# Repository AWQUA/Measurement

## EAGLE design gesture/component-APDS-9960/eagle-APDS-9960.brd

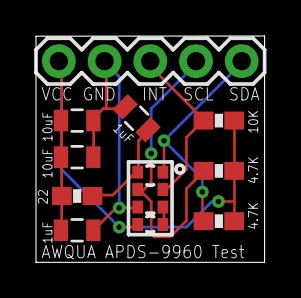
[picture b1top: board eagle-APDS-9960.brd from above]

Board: 2 copper layers, 12.7 x 12.6 mm, 10 parts (0 on the bottom side), 7 nets.

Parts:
C1, C4: 10uF; 0805
C2, C3: 1uF; 0805
JP1: 1X05
R1: 10K; 0603-RES
R2, R3: 4.7K; 0603-RES
R4: 22; 0603-RES
U1: APDS-9960

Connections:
GND: C1.1, C2.2, C3.1, C4.1, JP1.4, U1.6
INT: JP1.3, R1.1, U1.2
unnamed: U1.3, U1.4
unnamed: C3.2, R4.1, U1.8
SCL: JP1.2, R2.1, U1.7
SDA: JP1.1, R3.1, U1.1
VCC: C1.2, C2.1, C4.2, JP1.5, R1.2, R2.2, R3.2, R4.2, U1.5

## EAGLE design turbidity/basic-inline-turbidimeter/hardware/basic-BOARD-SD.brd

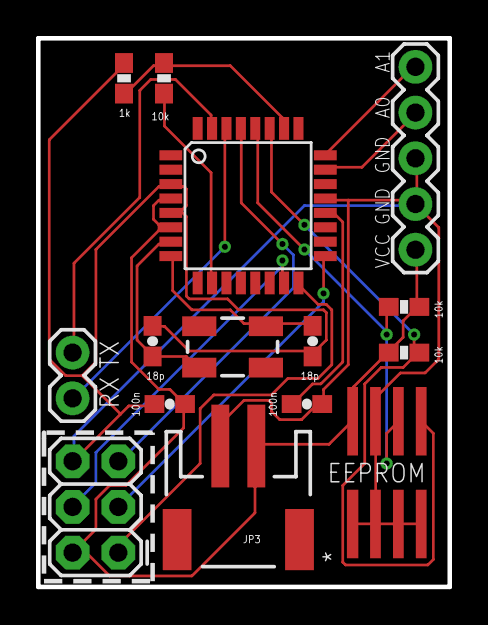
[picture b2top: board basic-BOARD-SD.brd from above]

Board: 2 copper layers, 22.9 x 30.5 mm, 17 parts (1 on the bottom side), 17 nets.

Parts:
C1, C2: 18p; 0603-CAP
C5, C8: 100n; 0603-CAP
EEPROM: AT24C256; SOIC8-LONGPAD
FRAME1: FRAME-LETTER; CREATIVE_COMMONS
IC1: MEGA8-AI; TQFP32-08
JP1: M02PTH; 1X02
JP2: 2X3
JP3: M02-JST-2MM-SMT; JST-2-SMD
JP4: 1X05
R1, R4, R5: 10k; 0603-RES
R2: 1k; 0603-RES
U$1: OSHW-LOGO-S
Y1: CRYSTAL-SMD-5X3

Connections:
AREF: C5.2, IC1.20
GND: C1.1, C2.1, C5.1, C8.2, EEPROM.1, EEPROM.2, EEPROM.3, EEPROM.4, EEPROM.7, IC1.3, IC1.5, IC1.21, JP2.6, JP3.2, JP4.3, JP4.4, R2.1
MISO: IC1.16, JP2.1
MOSI: IC1.15, JP2.4
PC0: IC1.23, JP4.2
PC1: IC1.24, JP4.1
PC3: IC1.26, R1.2, R2.2
PD6: IC1.10, R1.1
Q1: C2.2, IC1.8, Y1.1
Q2: C1.2, IC1.7, Y1.3
RST: IC1.29, JP2.5
RX: IC1.30, JP1.1
SCK: IC1.17, JP2.3
SCL: EEPROM.6, IC1.28, R5.2
SDA: EEPROM.5, IC1.27, R4.2
TX: IC1.31, JP1.2
VCC: C8.1, EEPROM.8, IC1.4, IC1.6, JP2.2, JP3.1, JP4.5, R4.1, R5.1

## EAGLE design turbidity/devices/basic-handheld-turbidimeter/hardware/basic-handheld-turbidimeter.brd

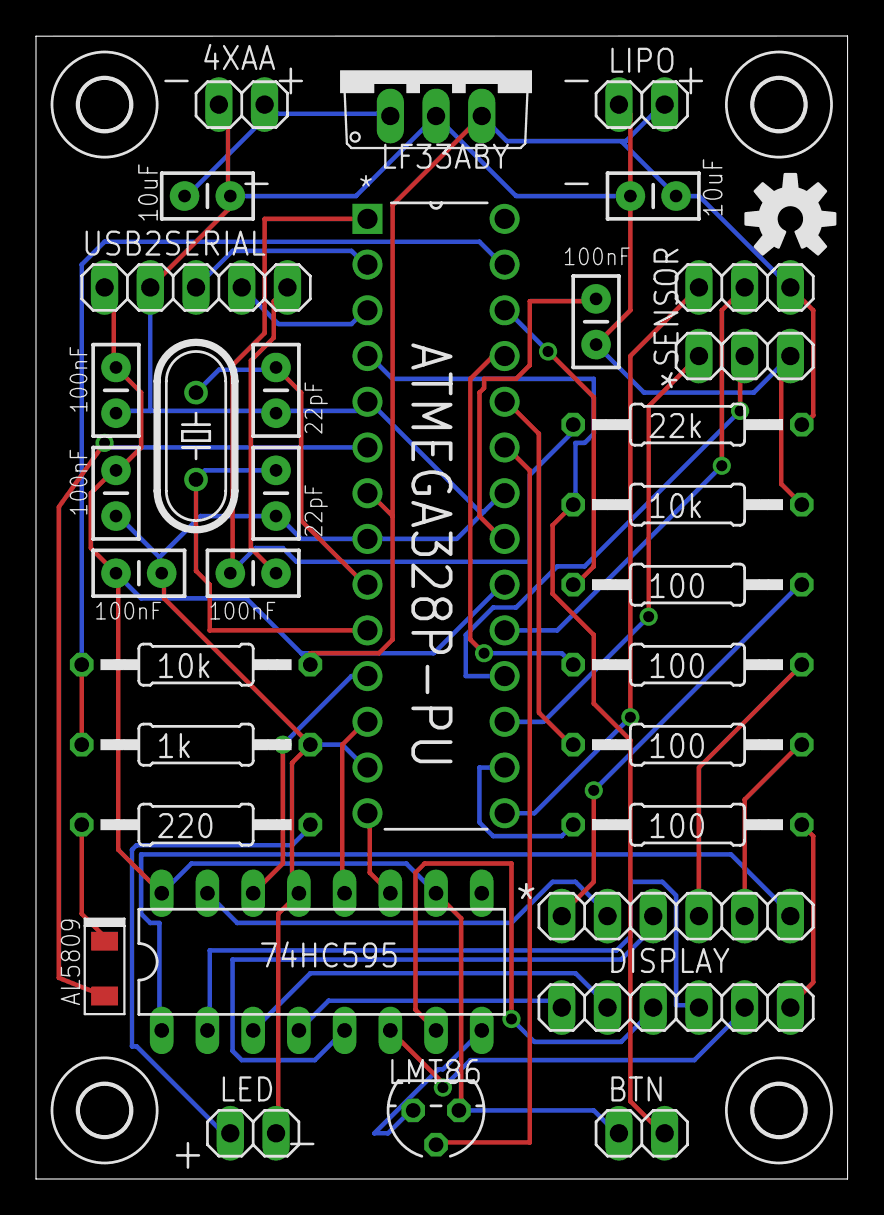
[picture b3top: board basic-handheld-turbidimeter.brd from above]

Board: 2 copper layers, 45.1 x 63.5 mm, 38 parts (0 on the bottom side), 39 nets.

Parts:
4XAA: 1X02
74HC595: 74HC595; DIL16
BTN: 1X02
C1, C2: 10uF; CAP-PTH-SMALLEZ
C3, C4: 22pF; CAP-PTH-SMALLEZ
C5, C6, C7, C8, C9: 100nF; CAP-PTH-SMALLEZ
DISPLAY: 1X06
JP4: 1X06
JP6: 1X03
LED: 1X02
LF33ABY: 7805TV; TO220V
LIPO: 1X02
LMT86: LM35CZ; TO92
Q1: 16.000; HC49/S
R1, R8: 10k; 0207/12
R2: 1k; 0207/12
R3, R4, R5, R6: 100; 0207/12
R7: 22k; 0207/12
R10: 220; 0207/12
SENSOR: 1X03
U1: ATMEGA328P-PU; DIP254P762X457-28
U$1, U$2, U$3, U$4: 2,8
U$5: OSHW-LOGO-M
U$6: AL5809
USB2SERIAL: 1X05

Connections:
3V3: 74HC595.10, 74HC595.16, BTN.1, C2.2, C5.1, C7.1, C8.2, LF33ABY.3, LIPO.2, LMT86.1, R1.2, R7.1, SENSOR.1, U1.7, U1.20, USB2SERIAL.1
595A: 74HC595.15, DISPLAY.5
595B: 74HC595.1, DISPLAY.1
595C: 74HC595.2, JP4.4
595D: 74HC595.3, JP4.2
595E: 74HC595.4, JP4.1
595F: 74HC595.5, DISPLAY.4
595G: 74HC595.6, JP4.5
595H: 74HC595.7, JP4.3
GND: 4XAA.1, 74HC595.8, 74HC595.13, C1.1, C2.1, C3.1, C4.1, C5.2, C6.2, C7.2, C8.1, JP6.3, LED.2, LF33ABY.2, LIPO.1, LMT86.3, R2.2, R8.2, U1.5, U1.8, U1.13, U1.22, USB2SERIAL.2
LED: LED.1, R10.1
unnamed: 4XAA.2, C1.2, LF33ABY.1
unnamed: R10.2, U$6.OUT
unnamed: C6.1, U1.21
unnamed: C9.2, USB2SERIAL.5
unnamed: DISPLAY.6, R3.2
unnamed: DISPLAY.3, R4.2
unnamed: DISPLAY.2, R5.2
unnamed: JP4.6, R6.1
PB0: 74HC595.11, U1.14
PB1: SENSOR.3, U1.15
PB2: R6.2, U1.16
PB3: JP6.1, U1.17
PB4: JP6.2, U1.18
PB5: SENSOR.2, U1.19
PB6: C3.2, Q1.1, U1.9
PB7: C4.2, Q1.2, U1.10
PC0: LMT86.2, U1.23
PC1: R5.1, U1.24
PC2: R4.1, U1.25
PC3: R3.1, U1.26
PC4: R1.1, R2.1, U1.27
PC6: C9.1, R7.2, U1.1
PD0: U1.2, USB2SERIAL.3
PD1: U1.3, USB2SERIAL.4
PD2: BTN.2, R8.1, U1.4
PD4: U1.6, U$6.IN
PD5: 74HC595.14, U1.11
PD6: 74HC595.12, U1.12

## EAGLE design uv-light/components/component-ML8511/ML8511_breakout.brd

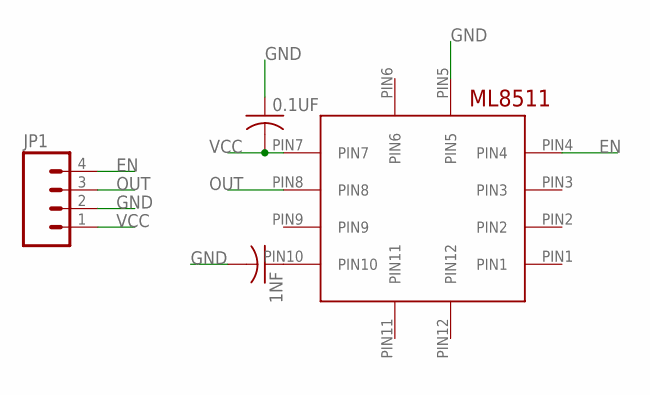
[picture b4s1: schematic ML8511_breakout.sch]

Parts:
0.1UF, 1NF: C-USC0603; C0603
JP1: M04PTH; 1X04
U$1: ML8511

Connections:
EN: JP1.4, U$1.PIN4
GND: 0.1UF.1, 1NF.2, JP1.2, U$1.PIN5
OUT: JP1.3, U$1.PIN8
TR: 1NF.1, U$1.PIN10
VCC: 0.1UF.2, JP1.1, U$1.PIN7

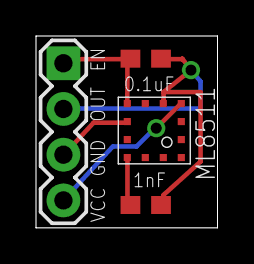
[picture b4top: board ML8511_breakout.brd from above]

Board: 2 copper layers, 10.1 x 10.7 mm, 4 parts (0 on the bottom side), 5 nets.

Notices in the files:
gesture/component-APDS-9960/eagle-APDS-9960.brd:
Released under Creative Commons license BY-SA 4.0
https://creativecommons.org/licenses/by-sa/4.0
parts and their libraries:
SparkFun-Sensors: Licensing: Creative Commons ShareAlike 4.0 International - https://creativecommons.org/licenses/by-sa/4.0
SparkFun-Connectors: Licensing: CC v3.0 Share-Alike You are welcome to use this library for commercial purposes.
